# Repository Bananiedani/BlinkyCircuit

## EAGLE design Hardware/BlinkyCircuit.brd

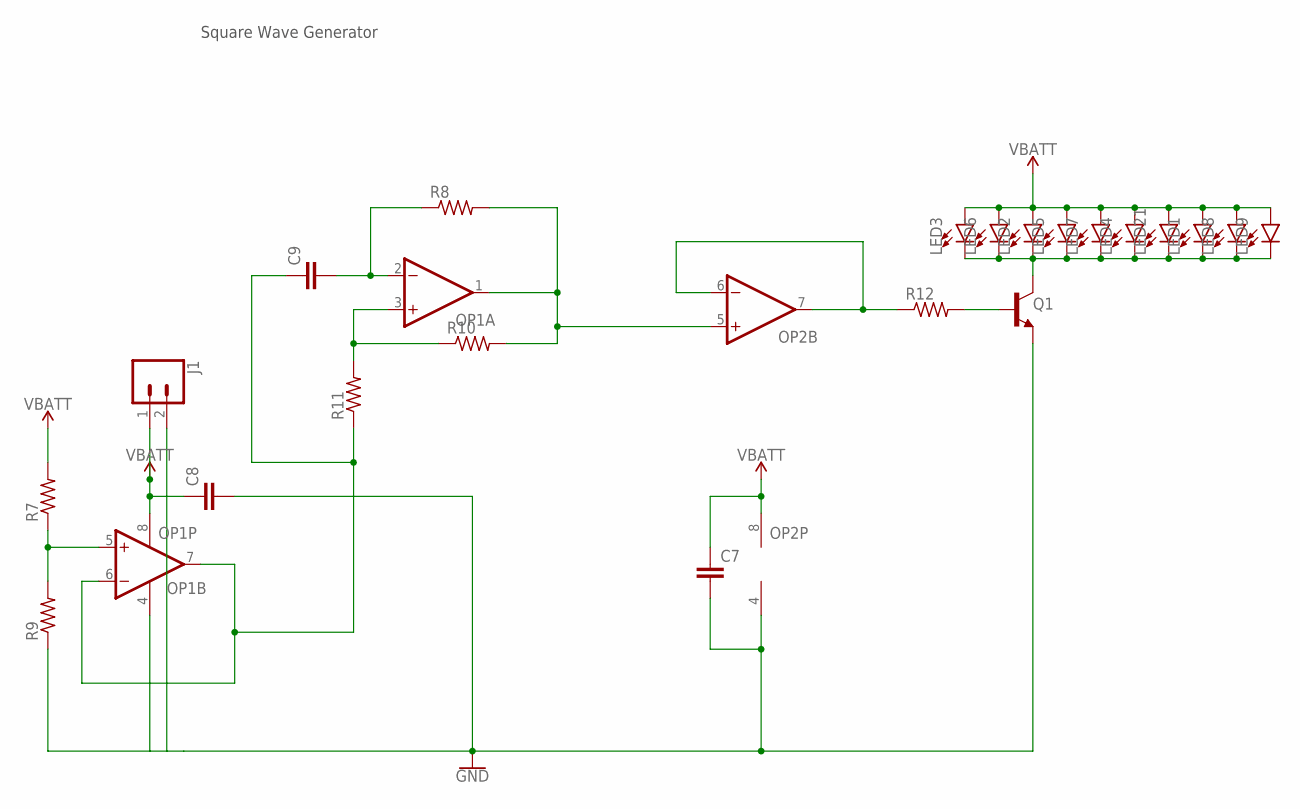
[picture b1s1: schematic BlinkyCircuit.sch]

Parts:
C7, C8, C9: CAPACITOR0603; C0603
J1: CONN_02; 1X02
LED1, LED2, LED3, LED4, LED5, LED6, LED7, LED8, LED9, LED21: LED5MM; LED_5MM
OP1, OP2: OP-DUALR; SO8
Q1: NPN-GENERIC; SOT23-3
R7, R8, R9, R10, R11, R12: RESISTOR0603; R0603

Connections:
GND: C7.2, C8.2, J1.2, OP1.4 (V-), OP2.4 (V-), Q1.2 (E), R9.1
unnamed: OP1.5 (+IN), R7.1, R9.2
unnamed: C9.2, OP1.2 (-IN), R8.1
unnamed: C9.1, OP1.6 (-IN), OP1.7 (OUT), R11.1
unnamed: OP1.3 (+IN), R10.1, R11.2
unnamed: OP1.1 (OUT), OP2.5 (+IN), R8.2, R10.2
unnamed: OP2.6 (-IN), OP2.7 (OUT), R12.1
unnamed: Q1.1 (B), R12.2
unnamed: LED1.K (C), LED2.K (C), LED3.K (C), LED4.K (C), LED5.K (C), LED6.K (C), LED7.K (C), LED8.K (C), LED9.K (C), LED21.K (C), Q1.3 (C)
V_BATT: C7.1, C8.1, J1.1, LED1.A, LED2.A, LED3.A, LED4.A, LED5.A, LED6.A, LED7.A, LED8.A, LED9.A, LED21.A, OP1.8 (V+), OP2.8 (V+), R7.2

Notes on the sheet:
Square Wave Generator

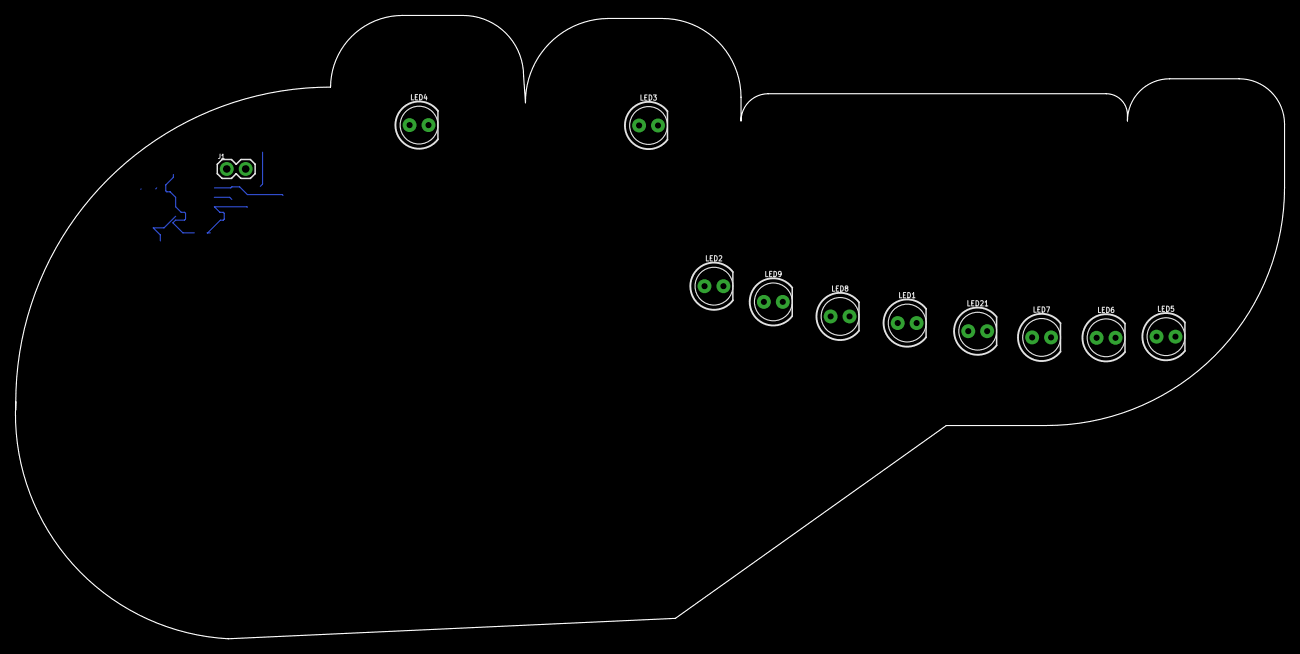
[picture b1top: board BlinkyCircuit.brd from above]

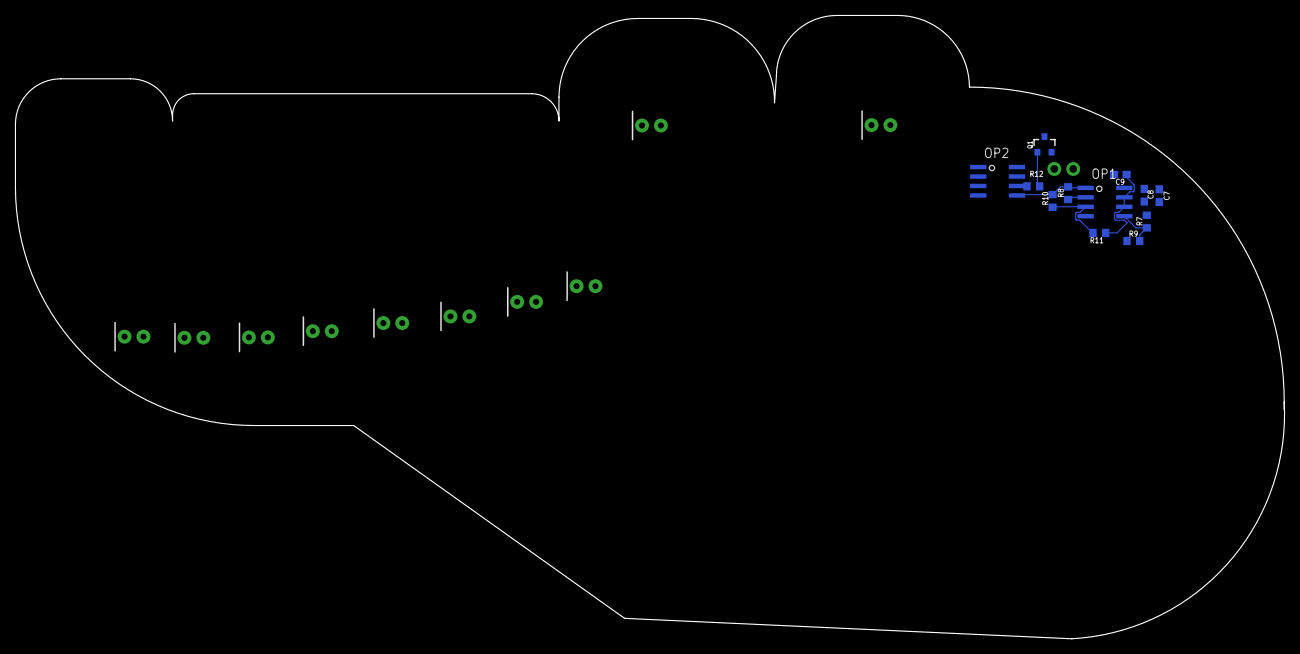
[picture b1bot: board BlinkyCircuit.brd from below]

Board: 2 copper layers, 170.5 x 83.7 mm, 23 parts (12 on the bottom side), 10 nets.

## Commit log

2021-02-20 add Document
2021-02-27 Adding Hardware Folder
2021-03-06 March 6 edits
2021-03-13 March 13 2021 BlinkyCircuit schematic
2021-03-13 March 13 2021 board edits
2021-03-22 March 22 2021 board edits
2021-03-22 March 22 2021 edits
2021-03-22 March 222 2021 edits
2021-03-27 March 27 2021 edits
2021-03-27 March 27 2021 board edits
